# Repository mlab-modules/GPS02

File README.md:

# GPS02B - MLAB Module for RTK Navigation

GPS02B is an accurate GNSS receiver module designed in the form of an MLAB module. This innovative design brings numerous advantages to the table, making it a choice for [RTK (Real-Time Kinematics)](https://en.wikipedia.org/wiki/Real-time_kinematic_positioning) navigation experiments. The GPS02B module is based on the uBlox receiver. There are multiple uBlox module types

  * [u-blox NEO-M8P](https://www.u-blox.com/en/product/neo-m8p-series) - With RTK functionality
  * [u-blox NEO-M9N](https://www.u-blox.com/en/product/neo-m9n-module) - High navigation rate GNSS module without RTK

The MLAB form factor provides several benefits for seamless integration and flexible usage. Here are some key advantages:

## Easy Integration and Compatibility

The GPS02B MLAB module follows the MLAB standard, making it easy to integrate into various MLAB-compatible systems and platforms. It ensures compatibility with other MLAB modules, allowing you to create custom configurations tailored to your specific requirements. The standardized pinout and interface simplify the process of connecting and interchanging modules within your MLAB ecosystem.

## Plug-and-Play Functionality

With its plug-and-play functionality, the GPS02B MLAB module simplifies the integration process. You can easily connect it to an MLAB system using standardized connectors, eliminating the need for complex wiring or soldering. This streamlined setup accelerates your development process and reduces time-to-market.

## Modular Expandability

The MLAB design philosophy revolves around modularity, enabling easy expansion and customization. The GPS02B module can be combined with other MLAB modules to enhance its capabilities or add new features. Whether you need additional sensors, communication interfaces, or processing power, the modular nature of MLAB allows for seamless expansion and adaptation to evolving project requirements.

## Robust and Reliable Construction

The GPS02B MLAB module is built to withstand demanding environments and provide reliable performance. Its sturdy construction ensures durability, making it suitable for applications that require long-term operation under challenging conditions. The module undergoes rigorous testing and quality control processes to deliver consistent and dependable results.

## Vast MLAB Ecosystem

By choosing the GPS02B MLAB module, you gain access to a vast ecosystem of MLAB modules and resources. The MLAB community offers a wide range of compatible modules, libraries, and development tools. You can leverage existing MLAB projects and community support to accelerate your development and benefit from the collective expertise of the MLAB community.

## Applications

The GPS02B MLAB module offers a wide range of applications in the field of RTK navigation and beyond. Here are a few examples:

- **Precision Agriculture**: Utilize the high-accuracy positioning capabilities of the GPS02B module for precise guidance of agricultural machinery, enabling optimized field operations and reduced input costs.

- **Geospatial Mapping**: Capture accurate geospatial data for surveying, mapping, and cartography applications. The GPS02B module provides reliable positioning information for creating detailed and precise maps.

- **Robotics**: Incorporate the GPS02B module into robotic systems for precise localization and navigation. Enable robots to navigate autonomously and perform tasks with high accuracy.

- **Asset Tracking**: Use the GPS02B module to track and monitor the movement of valuable assets in real-time, ensuring efficient logistics and enhanced security.

These are just a few examples of the many applications where the GPS02B MLAB module can be utilized. Its high accuracy, reliability, and compatibility with MLAB systems make it a versatile solution for a wide range of industries and projects.

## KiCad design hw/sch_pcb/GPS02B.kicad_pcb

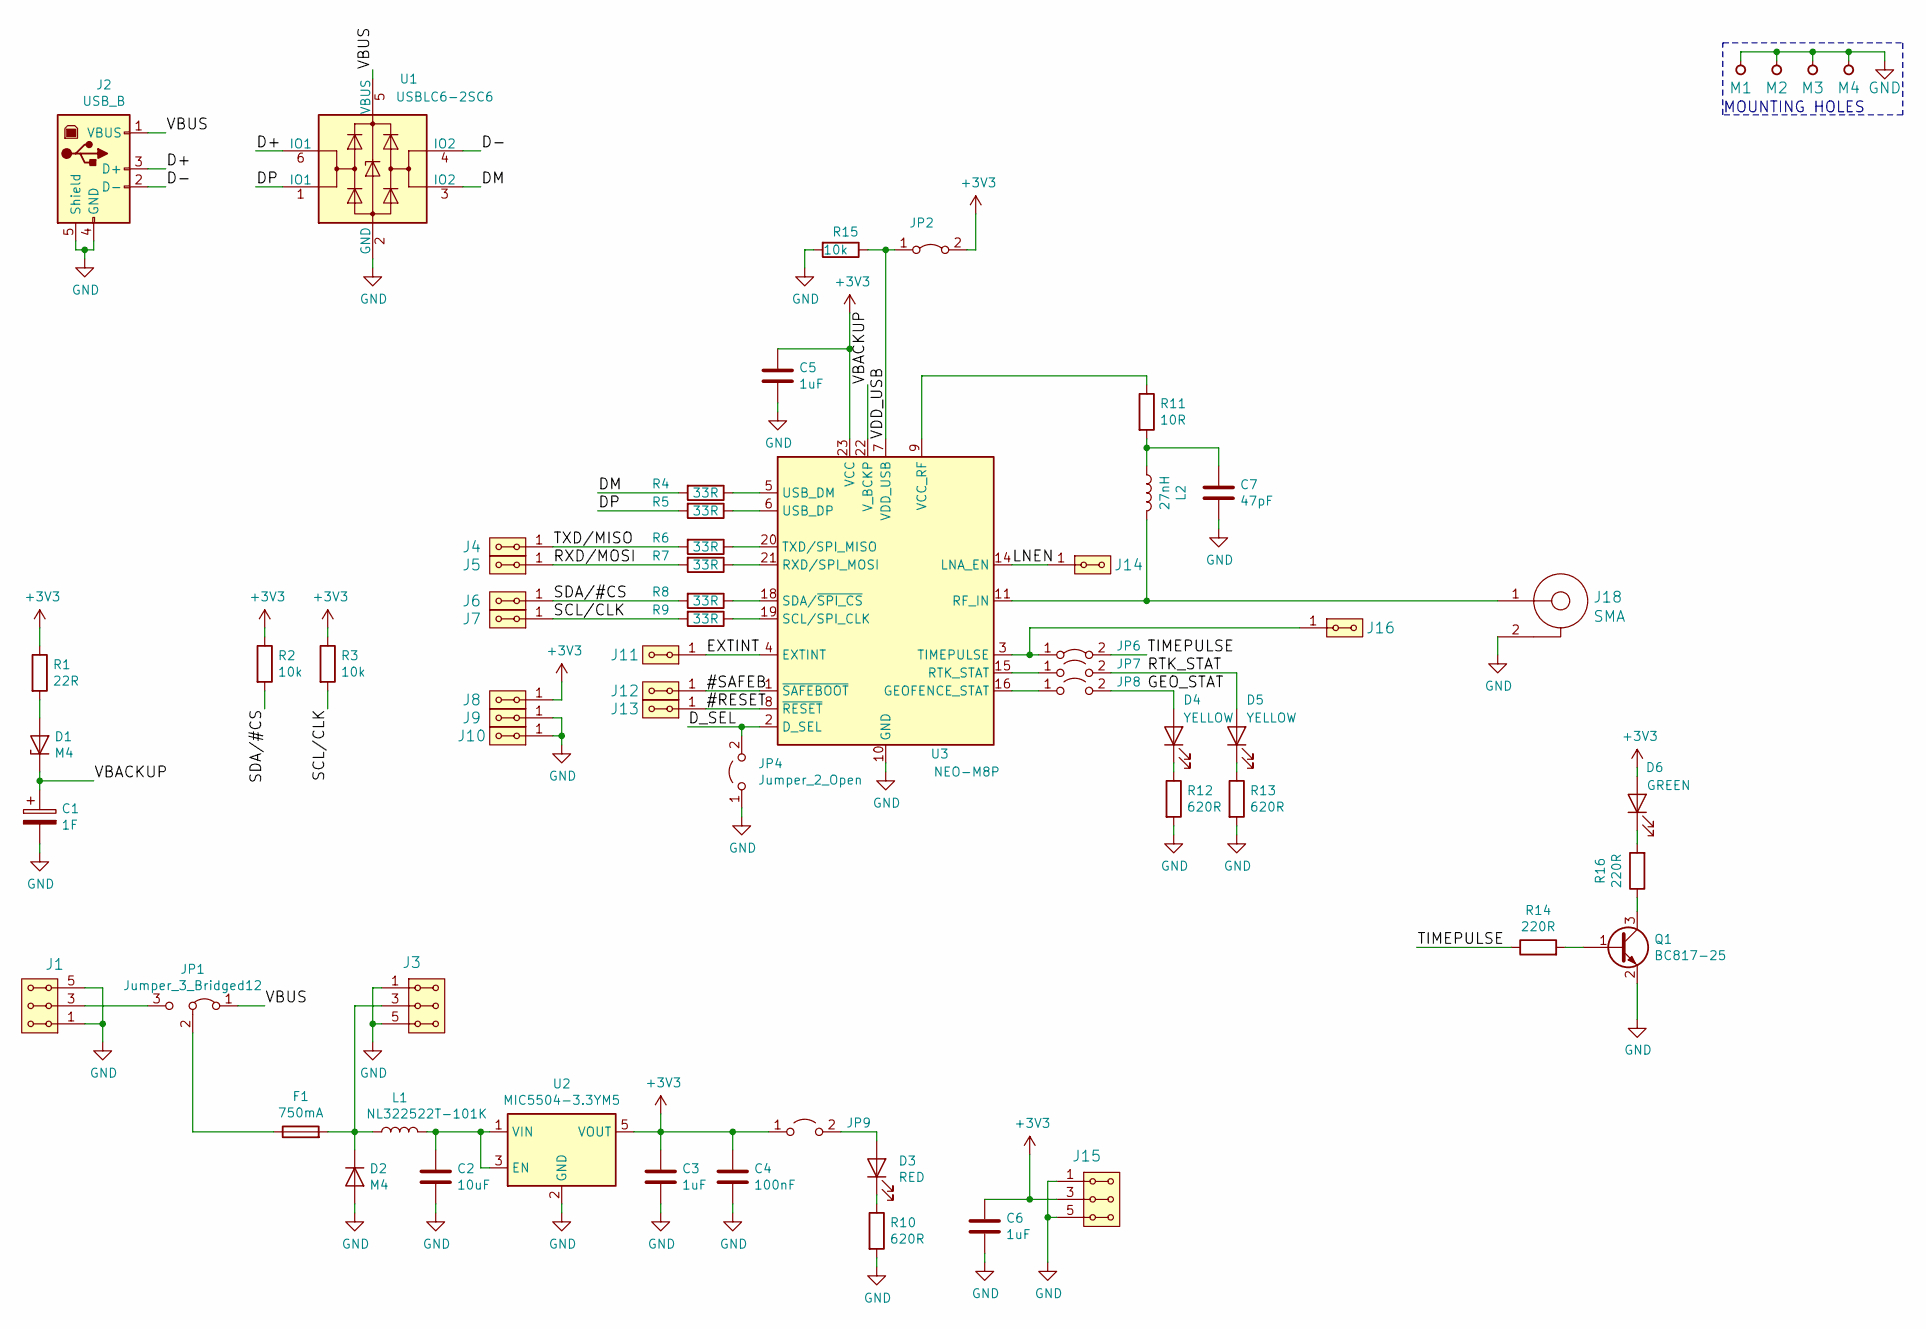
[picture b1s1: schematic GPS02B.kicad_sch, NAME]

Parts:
C1: 1F; CP_Radial_D8.0mm_P3.50mm
C2: 10uF; SMD-0805
C3, C5, C6: 1uF; SMD-0805
C4: 100nF; SMD-0805
C7: 47pF; SMD-0805
D1, D2: M4; D_SMA
D3: RED; LED_1206
D4, D5: YELLOW; LED_1206
D6: GREEN; LED_1206
F1: 750mA; 1812
J1, J3, J15: HEADER_2x03_PARALLEL; Straight_2x03
J2: USB_B; USB_B_OST_USB-B1HSxx_Horizontal
J4, J5, J6, J7, J8, J9, J10, J11, J12, J13, J14, J16: HEADER_2x01_PARALLEL; Straight_2x01
J18: SMA; SMA6251A13G50
JP1: Jumper_3_Bridged12; Straight_1x03
JP2, JP6: Jumper_2_Bridged; Straight_1x02
JP4: Jumper_2_Open; SolderJumper-2_P1.3mm_Open_RoundedPad1.0x1.5mm
JP7, JP8, JP9: Jumper_2_Open; Straight_1x02
L1: NL322522T-101K; L_1210_3225Metric
L2: 27nH; L_0402_1005Metric
M1, M2, M3, M4: HOLE; MountingHole_3mm
Q1: BC817-25; SOT-23
R1: 22R; SMD-0805
R2, R3, R15: 10k; SMD-0805
R4, R5, R6, R7, R8, R9: 33R; SMD-0805
R10, R12, R13: 620R; SMD-0805
R11: 10R; SMD-0805
R14, R16: 220R; SMD-0805
U1: USBLC6-2SC6; SOT-23-6
U2: MIC5504-3.3YM5; SOT-23-5
U3: NEO-M8P; ublox_NEO

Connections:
+3V3: C3.1, C4.1, C5.1, C6.1, D6.2 (A), J8.1, J8.2, J15.3, J15.4, JP2.2 (B), JP9.1 (A), R1.1, R2.1, R3.1, U2.5 (VOUT), U3.23 (VCC)
/#RESET: J13.1, J13.2, U3.8 (~RESET)
/#SAFEB: J12.1, J12.2, U3.1 (~SAFEBOOT)
/D+: J2.3 (D+), U1.6 (IO1)
/D-: J2.2 (D-), U1.4 (IO2)
/DM: R4.2, U1.3 (IO2)
/DP: R5.2, U1.1 (IO1)
/D_SEL: JP4.2 (B), U3.2 (D_SEL)
/EXTINT: J11.1, J11.2, U3.4 (EXTINT)
/GEO_STAT: D4.2 (A), JP8.2 (B)
/LNEN: J14.1, J14.2, U3.14 (LNA_EN)
/RTK_STAT: D5.2 (A), JP7.2 (B)
/RXD/MOSI: J5.1, J5.2, R7.2
/SCL/CLK: J7.1, J7.2, R3.2, R9.2
/SDA/#CS: J6.1, J6.2, R2.2, R8.2
/TIMEPULSE: JP6.2 (B), R14.1
/TXD/MISO: J4.1, J4.2, R6.2
/VBACKUP: C1.1, D1.1 (K), U3.22 (V_BCKP)
/VBUS: J2.1 (VBUS), JP1.1 (A), U1.5 (VBUS)
/VDD_USB: JP2.1 (A), R15.1, U3.7 (VDD_USB)
GND: C1.2, C2.2, C3.2, C4.2, C5.2, C6.2, C7.2, D2.2 (A), J1.1, J1.2, J1.5, J1.6, J2.4 (GND), J2.5 (Shield), J3.1, J3.2, J3.5, J3.6, J9.1, J9.2, J10.1, J10.2, J15.1, J15.2, J15.5, J15.6, J18.2, JP4.1 (A), M1.1, M2.1, M3.1, M4.1, Q1.2 (E), R10.2, R12.2, R13.2, R15.2, U1.2 (GND), U2.2 (GND), U3.10 (GND), U3.12 (GND), U3.13 (GND), U3.24 (GND)
unnamed: C2.1, L1.2, U2.1 (VIN), U2.3 (EN)
unnamed: C7.1, L2.1, R11.2
unnamed: D1.2 (A), R1.2
unnamed: D2.1 (K), F1.2, J3.3, J3.4, L1.1
unnamed: D3.1 (K), R10.1
unnamed: D3.2 (A), JP9.2 (B)
unnamed: D4.1 (K), R12.1
unnamed: D5.1 (K), R13.1
unnamed: D6.1 (K), R16.2
unnamed: F1.1, JP1.2 (C)
unnamed: J1.3, J1.4, JP1.3 (B)
unnamed: J16.1, J16.2, JP6.1 (A), U3.3 (TIMEPULSE)
unnamed: J18.1, L2.2, U3.11 (RF_IN)
unnamed: JP7.1 (A), U3.15 (RTK_STAT)
unnamed: JP8.1 (A), U3.16 (GEOFENCE_STAT)
unnamed: Q1.1 (B), R14.2
unnamed: Q1.3 (C), R16.1
unnamed: R4.1, U3.5 (USB_DM)
unnamed: R5.1, U3.6 (USB_DP)
unnamed: R6.1, U3.20 (TXD/SPI_MISO)
unnamed: R7.1, U3.21 (RXD/SPI_MOSI)
unnamed: R8.1, U3.18 (SDA/~SPI_CS)
unnamed: R9.1, U3.19 (SCL/SPI_CLK)
unnamed: R11.1, U3.9 (VCC_RF)

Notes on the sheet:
MOUNTING HOLES

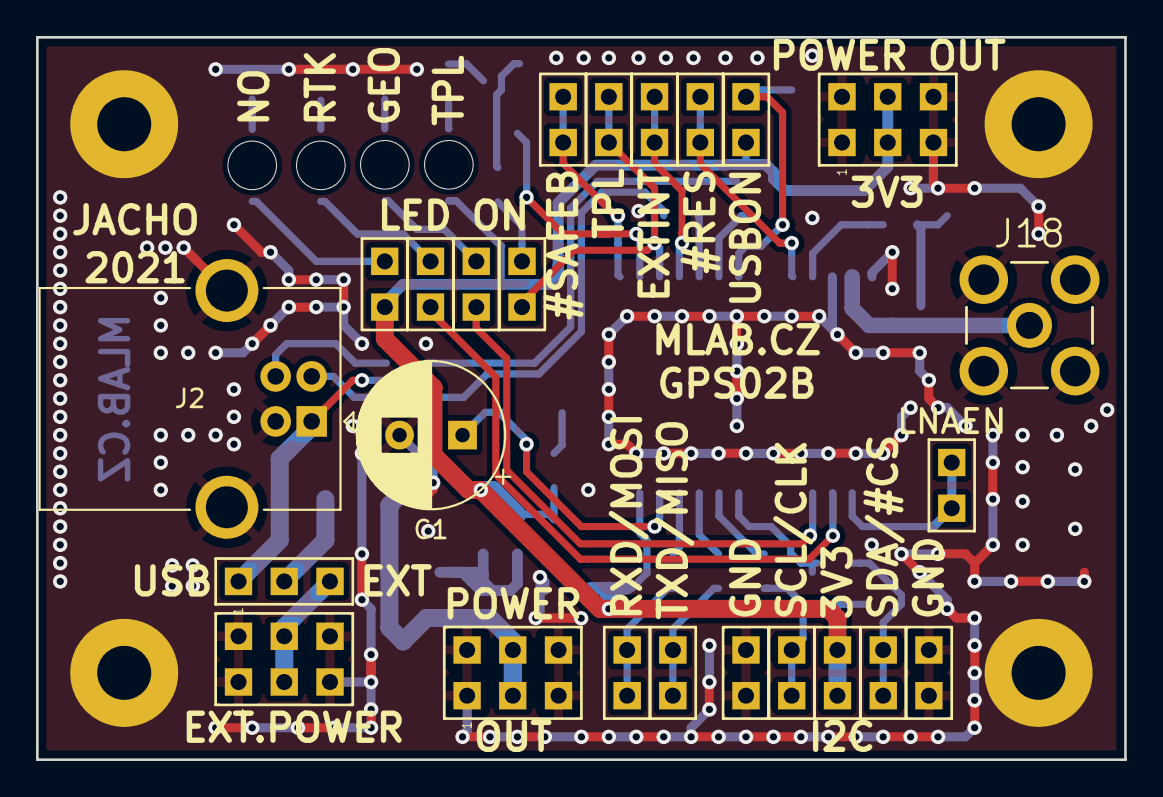
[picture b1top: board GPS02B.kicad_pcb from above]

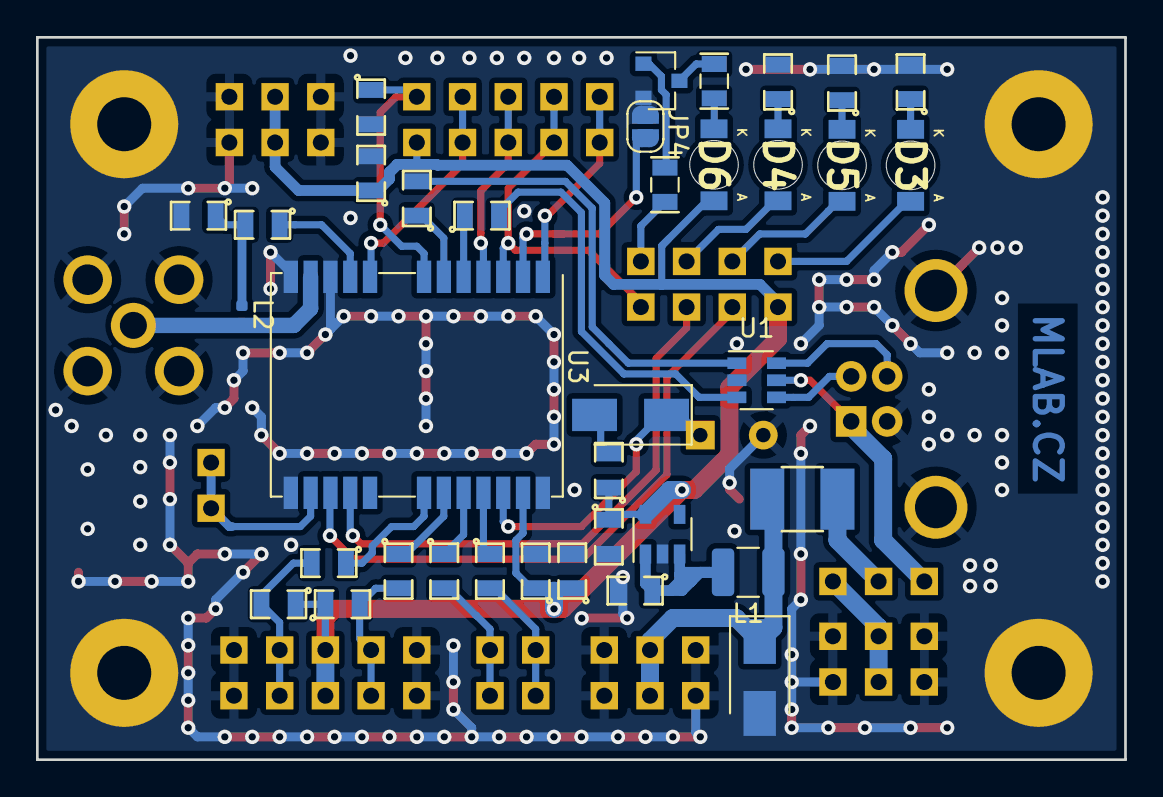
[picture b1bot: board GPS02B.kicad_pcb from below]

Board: 2 copper layers, 60.5 x 40.1 mm, 64 parts (36 on the bottom side), 45 nets.

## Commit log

2020-06-01 [MLABweb] Documentation edits; GPS02A
2020-06-01 Edit PCB
2020-06-03 Edit
2020-06-03 GPS02A BOM
2020-06-25 Module photos.
2020-10-28 Fix license.
2021-06-07 Kicad version update updating title block
2021-06-20 Update PCB component parameters from schematics.
2021-07-20 Edit #5 #4 #3 #1
2021-11-11 Edit bom
2021-11-24 Edit labels
2022-02-18 MLAB web edit.
2022-04-06 automated commit; add github actions
2022-04-06 Update actions products
2022-08-14 Update link to datasheet Update titleblock.
2023-02-14 update actions
2023-02-14 Update metadata files
2023-05-25 Update workflow files
2023-09-16 Update image to image_title
2023-09-16 Update status
2023-09-17 Update metadata.yaml
    select title image.
2024-03-13 Create tindie.md
    a copy of the content from Tindie.
